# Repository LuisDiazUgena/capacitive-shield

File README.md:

# capacitive-shield
Capacitive button shield for arduino

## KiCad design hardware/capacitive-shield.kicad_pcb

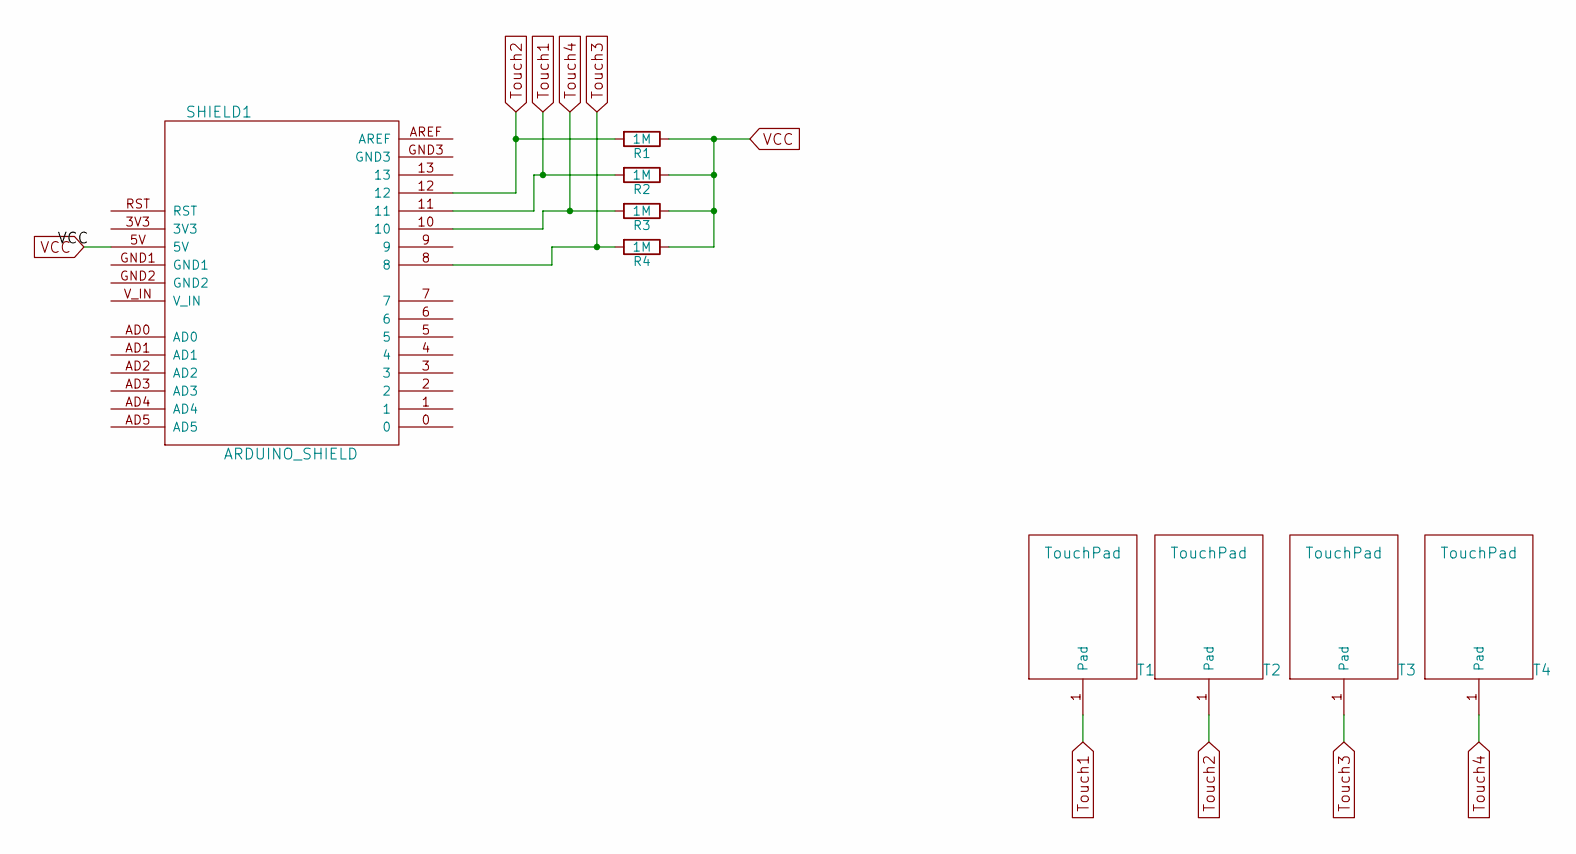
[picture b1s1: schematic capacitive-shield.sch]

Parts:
R1, R2, R3, R4: 1M; Resistor_Horizontal_RM20mm
SHIELD1: ARDUINO_SHIELD; ARDUINO_SHIELD_040pins
T1, T2, T3, T4: TouchPad

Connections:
Touch1: R2.2, SHIELD1.11, T1.1
Touch2: R1.2, SHIELD1.12, T2.1
Touch3: R4.2, SHIELD1.8, T3.1
Touch4: R3.2, SHIELD1.10, T4.1
VCC: R1.1, R2.1, R3.1, R4.1, SHIELD1.5V

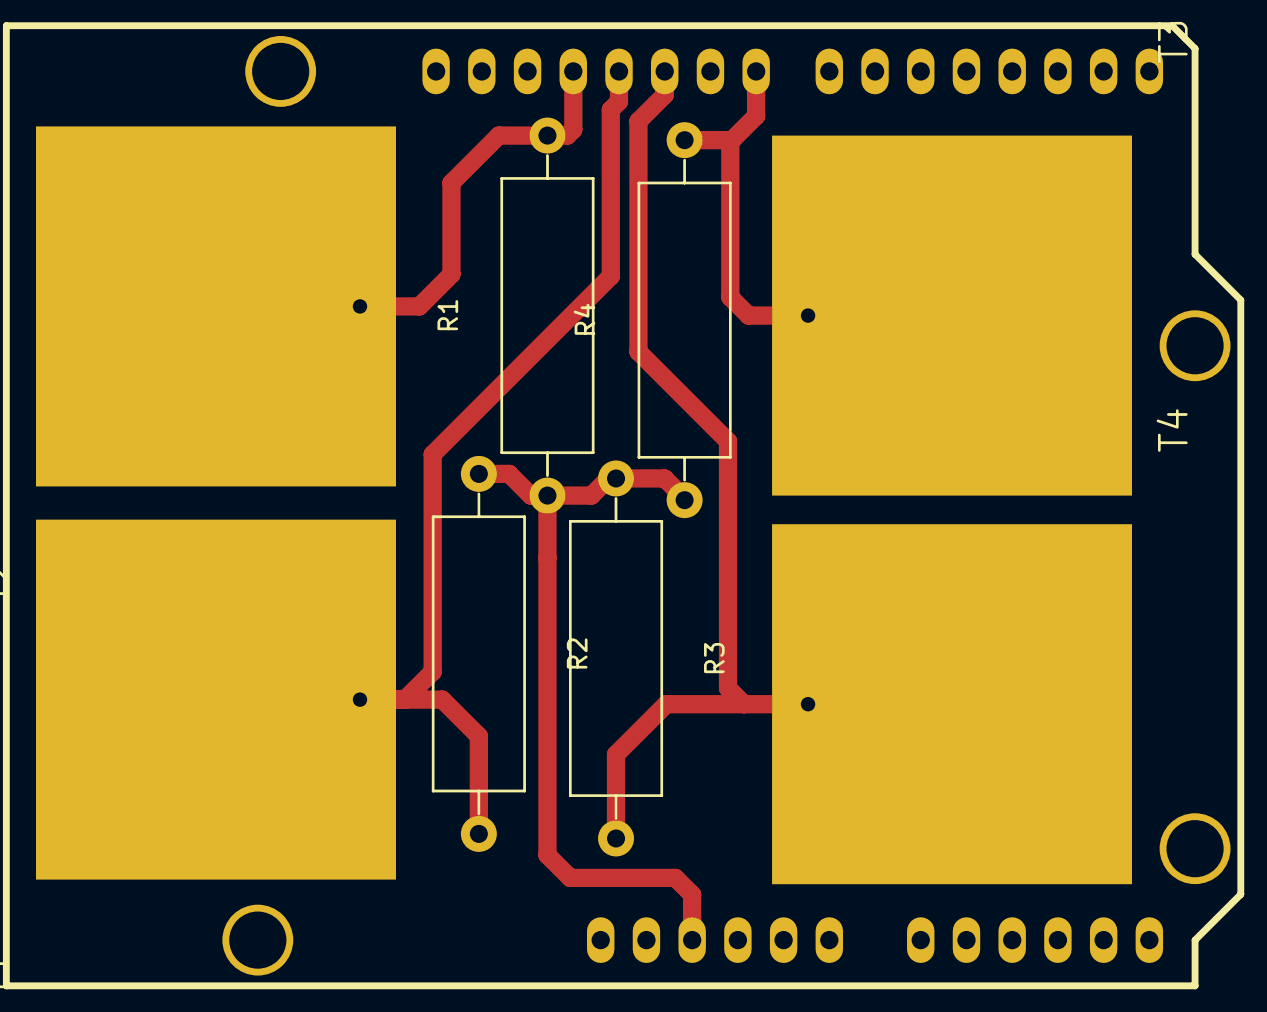
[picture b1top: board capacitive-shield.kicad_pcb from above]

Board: 2 copper layers, 9 parts (0 on the bottom side), 5 nets.

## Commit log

2015-08-26 Initial schematic and pcb board
2015-08-26 Added value test
2015-08-27 changed position of parts
2015-08-27 Created initial sketch
2015-09-16 removed unnecesary code
2015-09-16 Added piano example
